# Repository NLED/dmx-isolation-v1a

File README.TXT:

THERE IS NO WARRANTY FOR THE PROGRAM, TO THE EXTENT PERMITTED BY APPLICABLE LAW. 
EXCEPT WHEN OTHERWISE STATED IN WRITING THE COPYRIGHT HOLDERS AND/OR OTHER PARTIES 
PROVIDE THE PROGRAM “AS IS” WITHOUT WARRANTY OF ANY KIND, EITHER EXPRESSED OR IMPLIED,
INCLUDING, BUT NOT LIMITED TO, THE IMPLIED WARRANTIES OF MERCHANTABILITY AND FITNESS 
FOR A PARTICULAR PURPOSE. THE ENTIRE RISK AS TO THE QUALITY AND PERFORMANCE OF THE 
PROGRAM IS WITH YOU. SHOULD THE PROGRAM PROVE DEFECTIVE, YOU ASSUME THE COST OF ALL 
NECESSARY SERVICING, REPAIR OR CORRECTION.

 Original Author: Jeffrey Nygaard
 Company: Northern Lights Electronic Design, LLC
 Date: August 30, 2018
 Contact: JNygaard@NLEDshop.com
 Copyright© 2018 by Northern Lights Electronic Design, LLC. All Rights Reserved
 
;=============          www.NLEDShop.com/miscproducts          ============
;=============     www.NorthernLightsElectronicDesign.com       ============

This work is licensed under a Attribution-NonCommercial 4.0 International (CC BY-NC 4.0)
https://creativecommons.org/licenses/by-nc/4.0/legalcode

Free to use for personal use, but please attribute the original author.

Commercial licenses versions are available for a donation of any amount. Contact JNygaard@NLEDshop.com for details.

================================================================================================================

Ready-made devices are available for purchase, and large batch manufacturing of any device can be requested.
Please see the webpage www.NLEDShop.com/miscproducts

NLED is available for custom design and manufacturing, please contact via phone or email to discuss your project.

================================================================================================================

This simple device offers full electrical isolation for differential signals, such as DMX or RS485. Based on the 
venerable SN75176 transciever with a dual digital isolator and 1:1 DC-DC transformer. The device accepts a TTL input 
signal when setup to transmit and outputs a TTL signal when setup to receive. The differential conversion is handled
by the transciever. Accepts voltages from 5 to 12 volts, but always outputs TTL(0 to 5 volt) signals. This device 
works with many NLED products and controllers, but would also work with any Arduino or other embedded device as it 
communciates with standard TTL signals. For details on electrical isolation specifications, please use the BOM to 
look up part datasheets for details.

Minimum Input Voltage: 5 volts
Maximum Input Voltage: 12 volts
See CRE1S0505S3C  datasheet for electrical isolation details

Jumper settings:

	Close jumper VREG-J if voltage input is 5 volts.
	If voltage is higher than 5 volts, leave jumper open.

	Must close DIR-J to 'T' for transmitting, or 'R' for reception

	Jumper TERM is the signal terminator. Close jumper if receiving and
	the last or only receiver on the DMX network.

BOM:
	1x CRE1S0505S3C 
	1x SI8621AB-B-IS 
	1x SN75176BDR 
	1x AP2210K-5.0TRG1 
	2x C1Q 250 fuses
	1x 10uF 0805 capacitor
	2x 0.1uF 0805 capacitor
	1x 100pF 0805 capacitor
	1x 120 ohm 0805 resistor

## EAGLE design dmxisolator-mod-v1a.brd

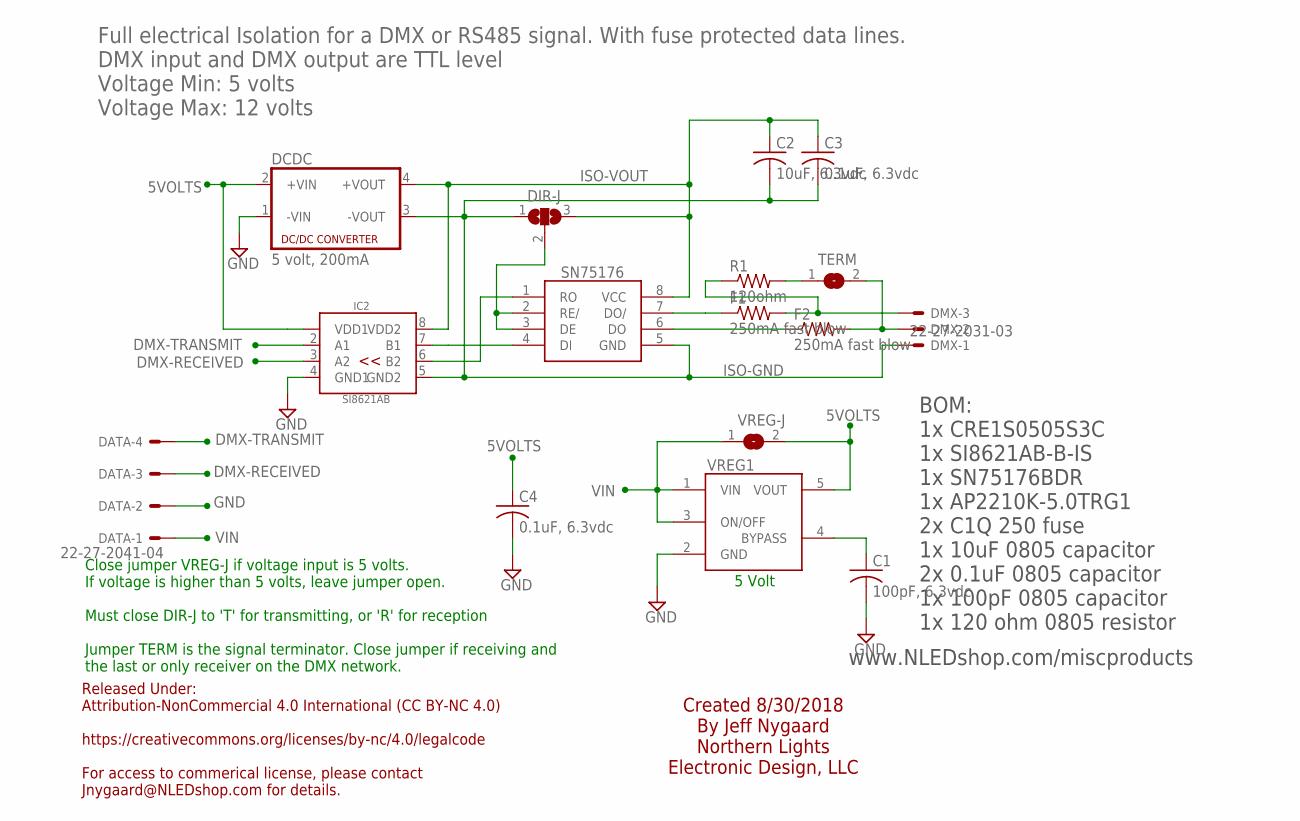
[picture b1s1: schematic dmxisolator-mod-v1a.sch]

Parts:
C1: 100pF, 6.3vdc; C0805
C2: 10uF, 6.3vdc; C0805
C3, C4: 0.1uF, 6.3vdc; C0805
DATA: 22-27-2041-04; 6410-04
DCDC: 5 volt, 200mA; NME
DIR-J: SJ2W; SJ_2
DMX: 22-27-2031-03; 6410-03
F1, F2: 250mA fast blow; R1206
IC2: SI8621AB-B-IS; SOIC-8
R1: 120ohm; R0805
SN75176: SN75176SMD; SOIC-8
TERM: SJ
VREG1: AP2210K; SOT25
VREG-J: SJ

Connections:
5VOLTS: C4.1, DCDC.2 (+VIN), IC2.1 (VDD1), VREG1.5 (VOUT), VREG-J.2
BYPASS: C1.1, VREG1.4 (BYPASS)
DMX-INV: DMX.3, F1.2, R1.1
DMX-POS: DMX.2, F2.2, TERM.2
DMX-RECEIVED: DATA.3, IC2.3 (A2)
DMX-TRANSMIT: DATA.4, IC2.2 (A1)
GND: C1.2, C4.2, DATA.2, DCDC.1 (-VIN), IC2.4 (GND1), VREG1.2 (GND)
ISO-GND: C2.2, C3.2, DCDC.3 (-VOUT), DIR-J.1, DMX.1, IC2.5 (GND2), SN75176.5 (GND)
ISO-VOUT: C2.1, C3.1, DCDC.4 (+VOUT), DIR-J.3, IC2.8 (VDD2), SN75176.8 (VCC)
unnamed: R1.2, TERM.1
unnamed: F1.1, SN75176.7 (DO/)
unnamed: F2.1, SN75176.6 (DO)
unnamed: DIR-J.2, SN75176.2 (RE/), SN75176.3 (DE)
unnamed: IC2.6 (B2), SN75176.1 (RO)
unnamed: IC2.7 (B1), SN75176.4 (DI)
VIN: DATA.1, VREG1.1 (VIN), VREG1.3 (ON/OFF), VREG-J.1

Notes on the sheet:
Created 8/30/2018 By Jeff Nygaard Northern Lights Electronic Design, LLC
Released Under: Attribution-NonCommercial 4.0 International (CC BY-NC 4.0) https://creativecommons.org/licenses/by-nc/4.0/legalcode For access to commerical license, please contact Jnygaard@NLEDshop.com for details.
5 Volt
Full electrical Isolation for a DMX or RS485 signal. With fuse protected data lines. DMX input and DMX output are TTL level Voltage Min: 5 volts Voltage Max: 12 volts
Close jumper VREG-J if voltage input is 5 volts. If voltage is higher than 5 volts, leave jumper open. Must close DIR-J to 'T' for transmitting, or 'R' for reception Jumper TERM is the signal terminator. Close jumper if receiving and the last or only receiver on the DMX network.
www.NLEDshop.com/miscproducts
BOM: 1x CRE1S0505S3C 1x SI8621AB-B-IS 1x SN75176BDR 1x AP2210K-5.0TRG1 2x C1Q 250 fuse 1x 10uF 0805 capacitor 2x 0.1uF 0805 capacitor 1x 100pF 0805 capacitor 1x 120 ohm 0805 resistor

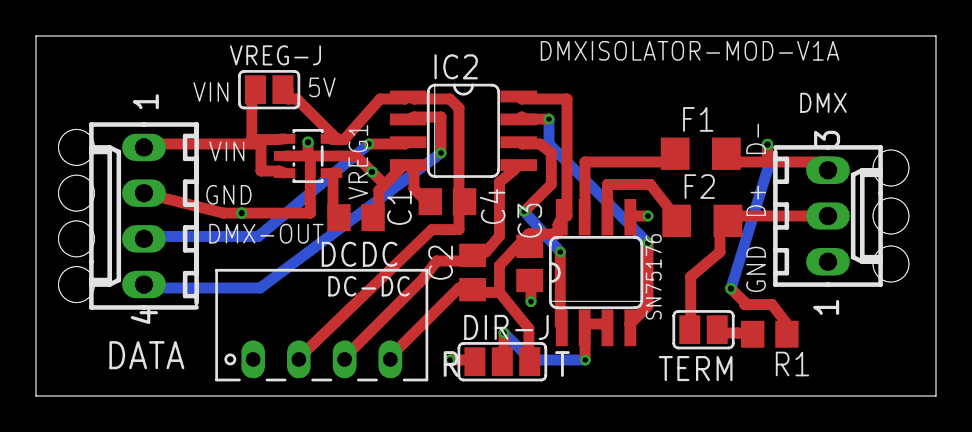
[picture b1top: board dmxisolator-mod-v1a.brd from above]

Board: 2 copper layers, 50.0 x 20.0 mm, 16 parts (0 on the bottom side), 16 nets.

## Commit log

2018-08-31 Initial

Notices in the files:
dmxisolator-mod-v1a.brd:
Copyright 2018
